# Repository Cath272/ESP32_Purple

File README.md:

# ESP32_Purple

The ESP32 PURPLE was build because i wanted to design my own esp32 based microcontroller with a few extra features.

Features:
-Esp32 Module,

-CH343P usb to uart Ic,

-3.3V AMS117 power supply,

-USB TYPE-C port with c to c cable support, 

-MicroSD card slot,

-14Pin Connector for a ST7735 Display(0.5mm pitch),

PCB view:

Schematic:

Components Pinout:

LCD: DC:IO26 , MOSI:IO23, SCK:IO18, CS:IO5

MicroSD: MISO:IO19, SCK:IO18, MOSI:IO23 , CS_SD:IO5

Final Assembled product:

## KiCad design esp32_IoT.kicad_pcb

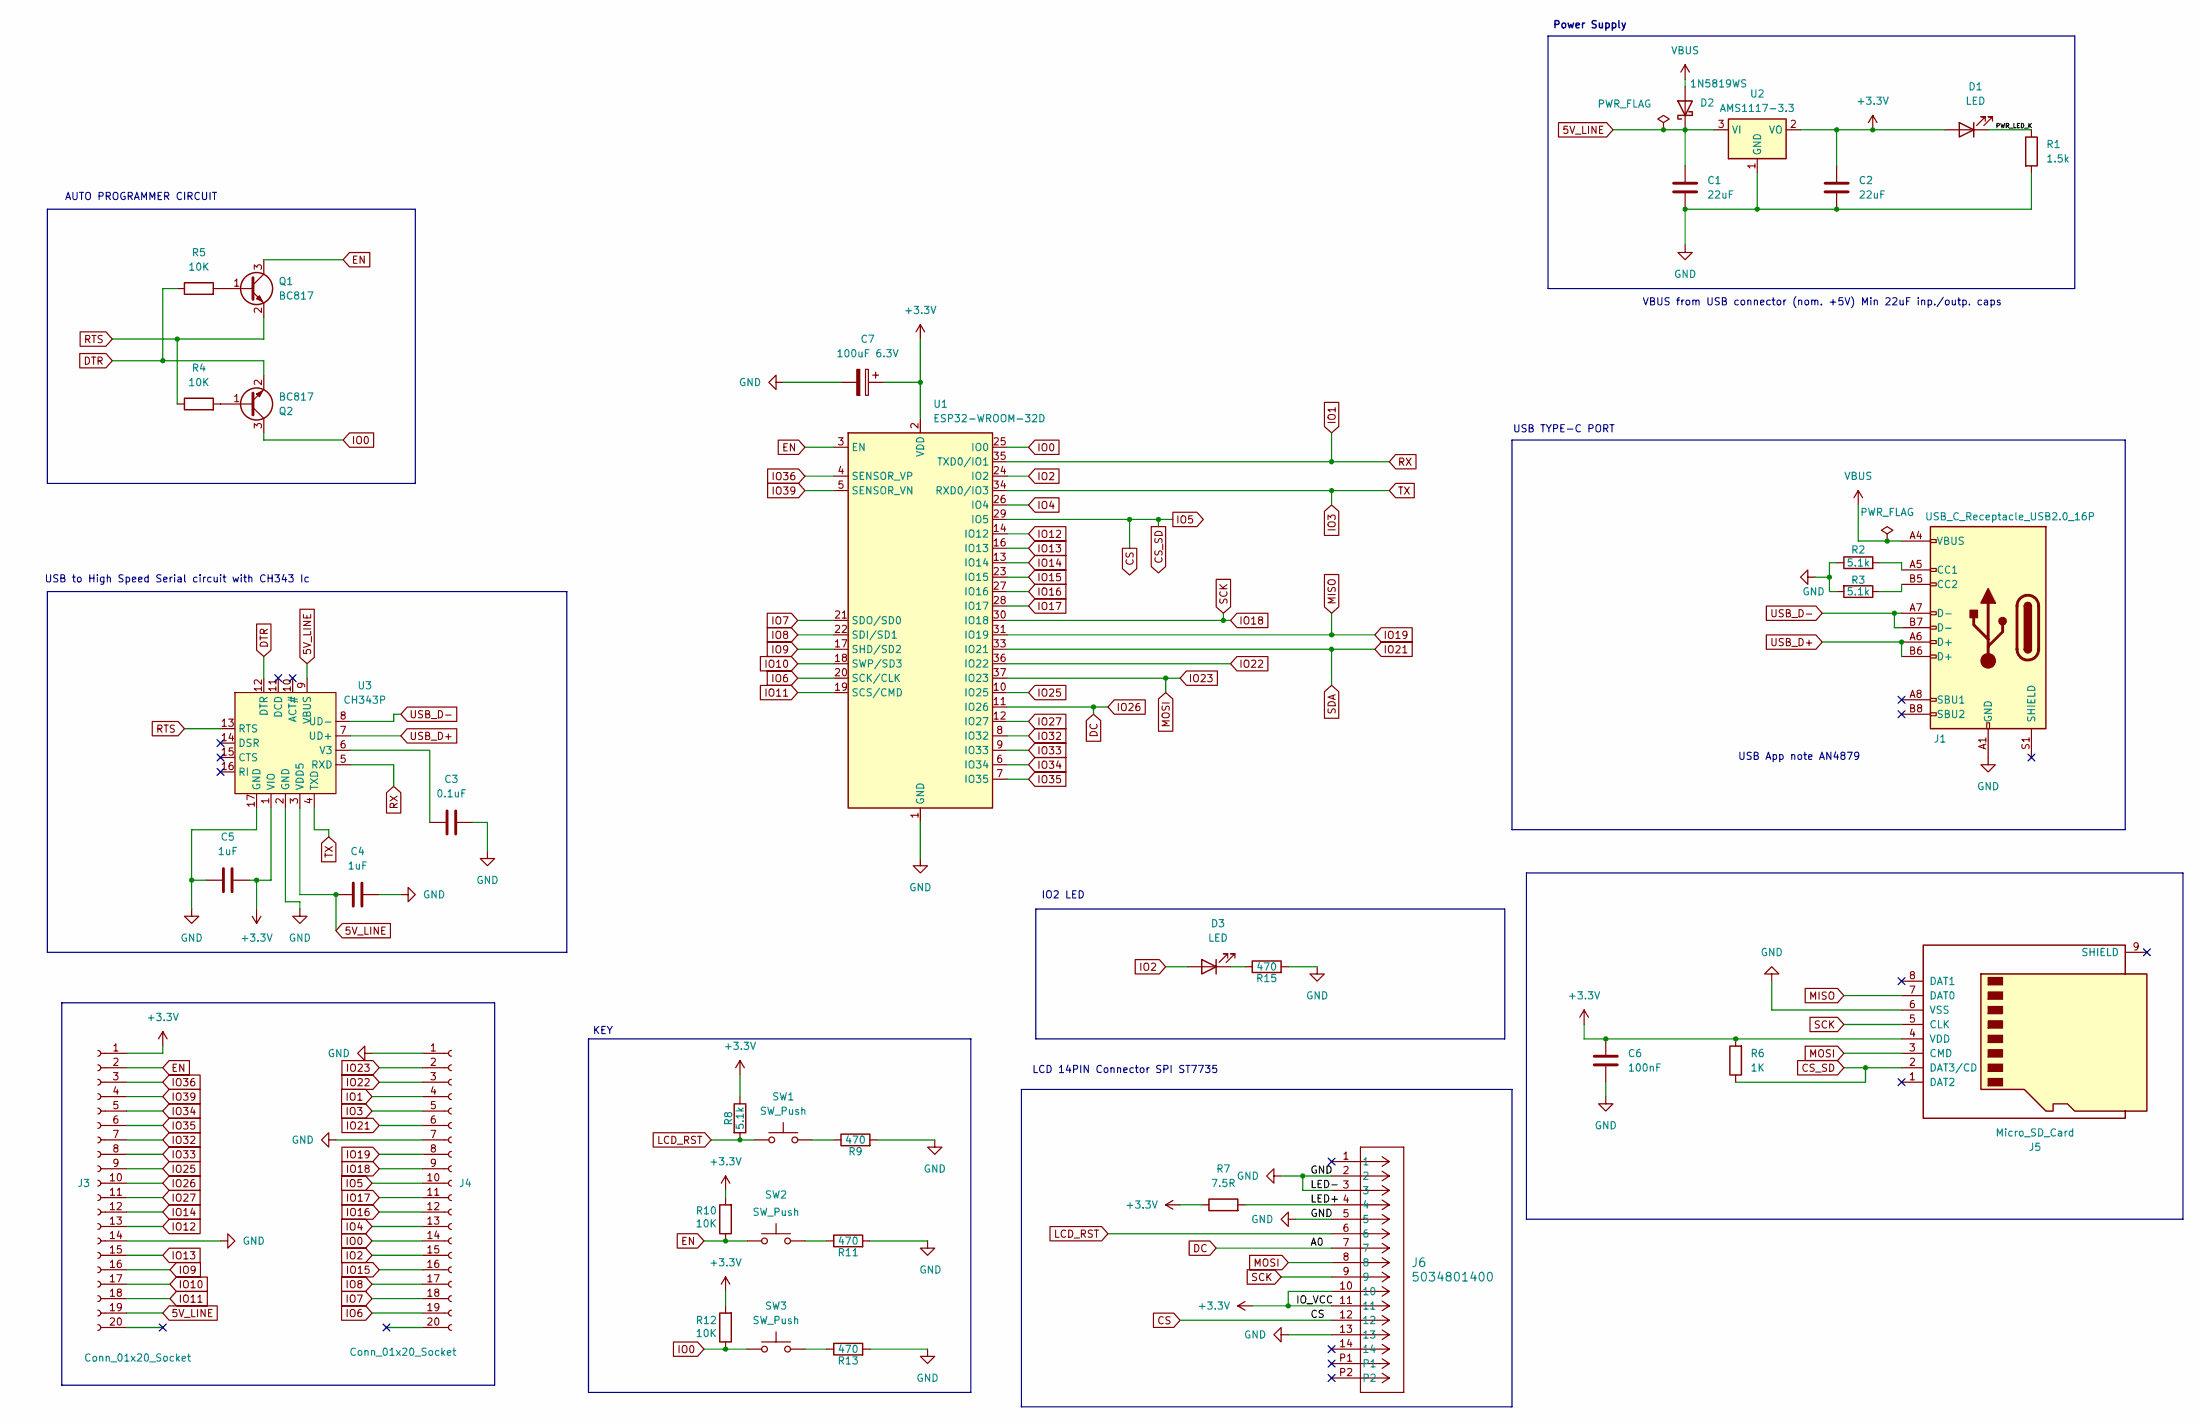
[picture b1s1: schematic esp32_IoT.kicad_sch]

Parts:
C1, C2: 22uF; C_0805_2012Metric
C3: 0.1uF; C_0402_1005Metric
C4, C5: 1uF; C_0402_1005Metric
C6: 100nF; C_0402_1005Metric_Pad0.74x0.62mm_HandSolder
C7: 100uF 6.3V; CP_EIA-3528-15_AVX-H_Pad1.50x2.35mm_HandSolder
D1, D3: LED; LED_0603_1608Metric
D2: 1N5819WS; D_SOD-323
J1: USB_C_Receptacle_USB2.0_16P; USB_C_Receptacle_GCT_USB4105-xx-A_16P_TopMnt_Horizontal
J3, J4: Conn_01x20_Socket; PinSocket_1x20_P2.54mm_Vertical
J5: Micro_SD_Card; SUNTECH_ST-TF-003A
J6: 5034801400; Hirose_FH12-14S-0.5SH_1x14-1MP_P0.50mm_Horizontal
Q1, Q2: BC817; SOT-23
R1: 1.5k; R_0402_1005Metric
R2, R3, R8: 5.1k; R_0402_1005Metric
R4, R5, R10, R12: 10K; R_0402_1005Metric
R6: 1K; R_0402_1005Metric
R7: 7.5R; R_0402_1005Metric
R9, R11, R13, R15: 470; R_0402_1005Metric
SW1, SW2, SW3: SW_Push; SW_SPST_PTS810
U1: ESP32-WROOM-32D
U2: AMS1117-3.3; SOT-223-3_TabPin2
U3: CH343P; TQFN-16-1EP_3x3mm_P0.5mm_EP1.6x1.6mm

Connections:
5V_LINE: C1.1, C4.1, D2.1 (K), J3.19, U2.3 (VI), U3.3 (VDD5), U3.9 (VBUS)
+3.3V: C2.1, C5.2, C6.1, C7.1, D1.2 (A), J3.1, J5.4 (VDD), J6.10, J6.11, R6.2, R7.1, R8.1, R10.2, R12.2, U1.2 (VDD), U2.2 (VO), U3.1 (VIO)
/LED+: J6.4, R7.2
/PWR_LED_K: D1.1 (K), R1.1
CS: J4.10, J5.2 (DAT3/CD), J6.12, R6.1, U1.29 (IO5)
DC: J3.10, J6.7, U1.11 (IO26)
DTR: Q2.2 (E), R5.1, U3.12 (DTR)
EN: J3.2, Q1.3 (C), R10.1, SW2.1, U1.3 (EN)
GND: C1.2, C2.2, C3.2, C4.2, C5.1, C6.2, C7.2, J1.A1 (GND), J1.A12 (GND), J1.B1 (GND), J1.B12 (GND), J3.14, J4.1, J4.7, J5.6 (VSS), J6.2, J6.3, J6.5, J6.13, R1.2, R2.1, R3.2, R9.2, R11.2, R13.2, R15.2, U1.1 (GND), U1.15 (GND), U1.38 (GND), U1.39 (GND), U2.1 (GND), U3.2 (GND), U3.17 (GND)
IO0: J4.14, Q2.3 (C), R12.1, SW3.1, U1.25 (IO0)
IO1: J4.4, U1.35 (TXD0/IO1), U3.5 (RXD)
IO2: D3.2 (A), J4.15, U1.24 (IO2)
IO3: J4.5, U1.34 (RXD0/IO3), U3.4 (TXD)
IO4: J4.13, U1.26 (IO4)
IO6: J4.19, U1.20 (SCK/CLK)
IO7: J4.18, U1.21 (SDO/SD0)
IO8: J4.17, U1.22 (SDI/SD1)
IO9: J3.16, U1.17 (SHD/SD2)
IO10: J3.17, U1.18 (SWP/SD3)
IO11: J3.18, U1.19 (SCS/CMD)
IO12: J3.13, U1.14 (IO12)
IO13: J3.15, U1.16 (IO13)
IO14: J3.12, U1.13 (IO14)
IO15: J4.16, U1.23 (IO15)
IO16: J4.12, U1.27 (IO16)
IO17: J4.11, U1.28 (IO17)
IO18: J4.9, J5.5 (CLK), J6.9, U1.30 (IO18)
IO19: J4.8, J5.7 (DAT0), U1.31 (IO19)
IO21: J4.6, U1.33 (IO21)
IO22: J4.3, U1.36 (IO22)
IO23: J4.2, J5.3 (CMD), J6.8, U1.37 (IO23)
IO25: J3.9, U1.10 (IO25)
IO27: J3.11, U1.12 (IO27)
IO32: J3.7, U1.8 (IO32)
IO33: J3.8, U1.9 (IO33)
IO34: J3.5, U1.6 (IO34)
IO35: J3.6, U1.7 (IO35)
IO36: J3.3, U1.4 (SENSOR_VP)
IO39: J3.4, U1.5 (SENSOR_VN)
LCD_RST: J6.6, R8.2, SW1.1; also elsewhere on the board
unnamed: D3.1 (K), R15.1
unnamed: J1.A5 (CC1), R2.2
unnamed: J1.B5 (CC2), R3.1
unnamed: Q1.1 (B), R5.2
unnamed: Q2.1 (B), R4.2
unnamed 45: R9.1, SW1.2; also elsewhere on the board
unnamed: R11.1, SW2.2
unnamed: R13.1, SW3.2
unnamed: C3.1, U3.6 (V3)
RTS: Q1.2 (E), R4.1, U3.13 (RTS)
USB_D+: J1.A6 (D+), J1.B6 (D+), U3.7 (UD+)
USB_D-: J1.A7 (D-), J1.B7 (D-), U3.8 (UD-)
VBUS: D2.2 (A), J1.A4 (VBUS), J1.A9 (VBUS), J1.B4 (VBUS), J1.B9 (VBUS)

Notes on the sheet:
LCD 14PIN Connector SPI ST7735
KEY
IO2 LED
USB to High Speed Serial circuit with CH343 Ic
AUTO PROGRAMMER CIRCUIT
VBUS from USB connector (nom. +5V) Min 22uF inp./outp. caps
USB App note AN4879
Power Supply
USB TYPE-C PORT

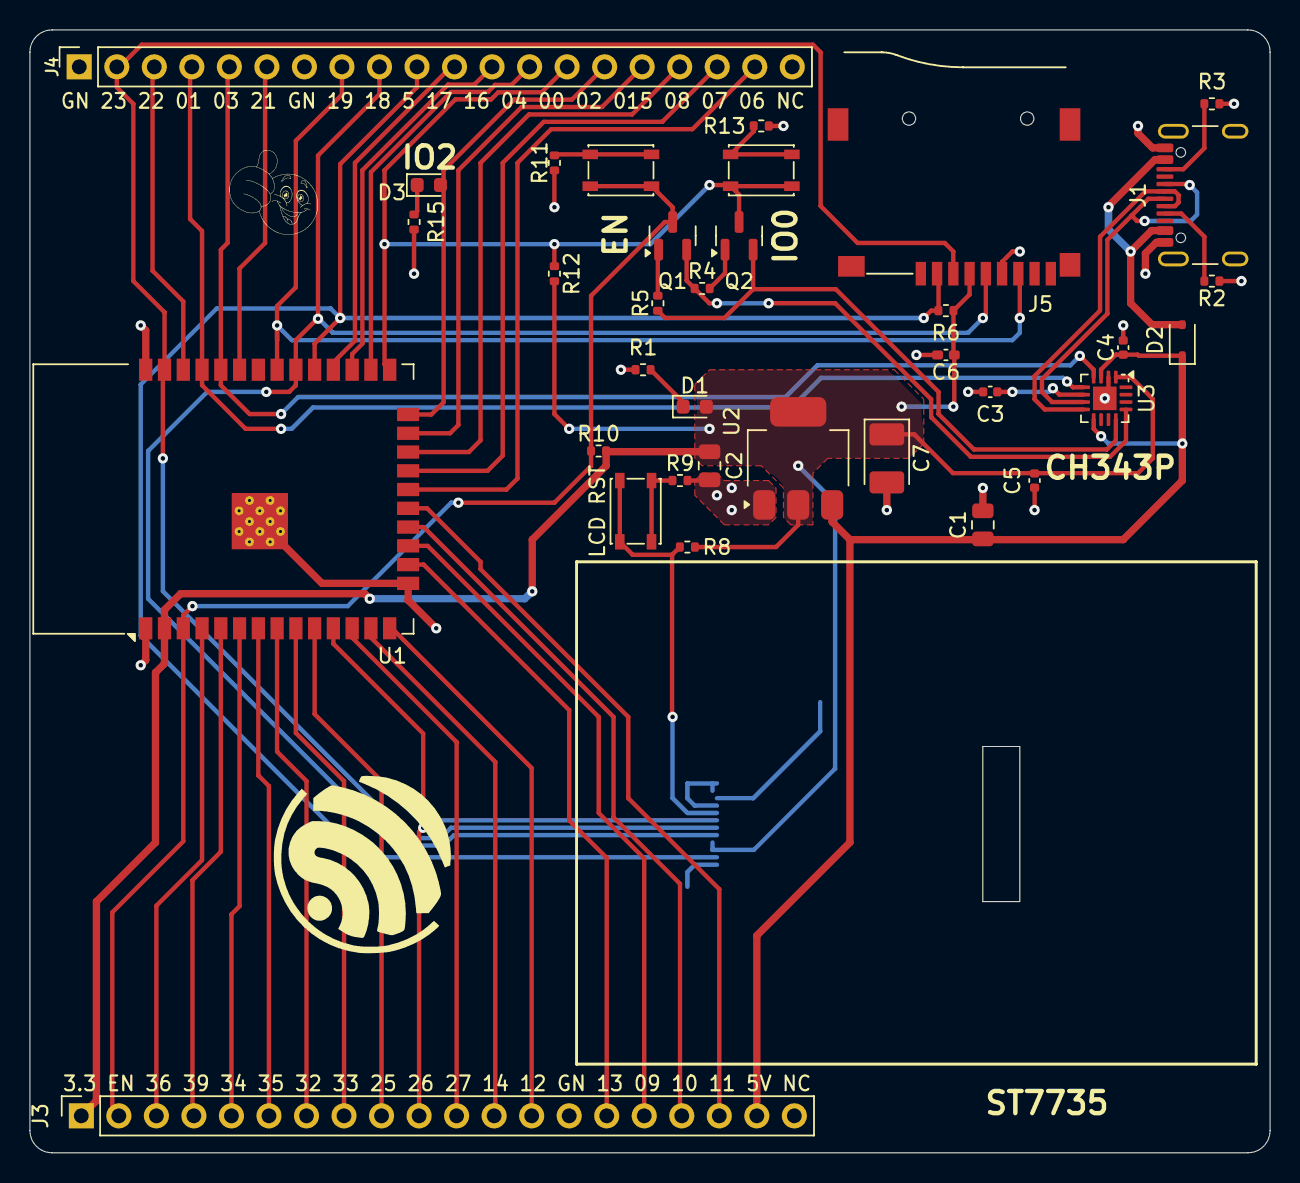
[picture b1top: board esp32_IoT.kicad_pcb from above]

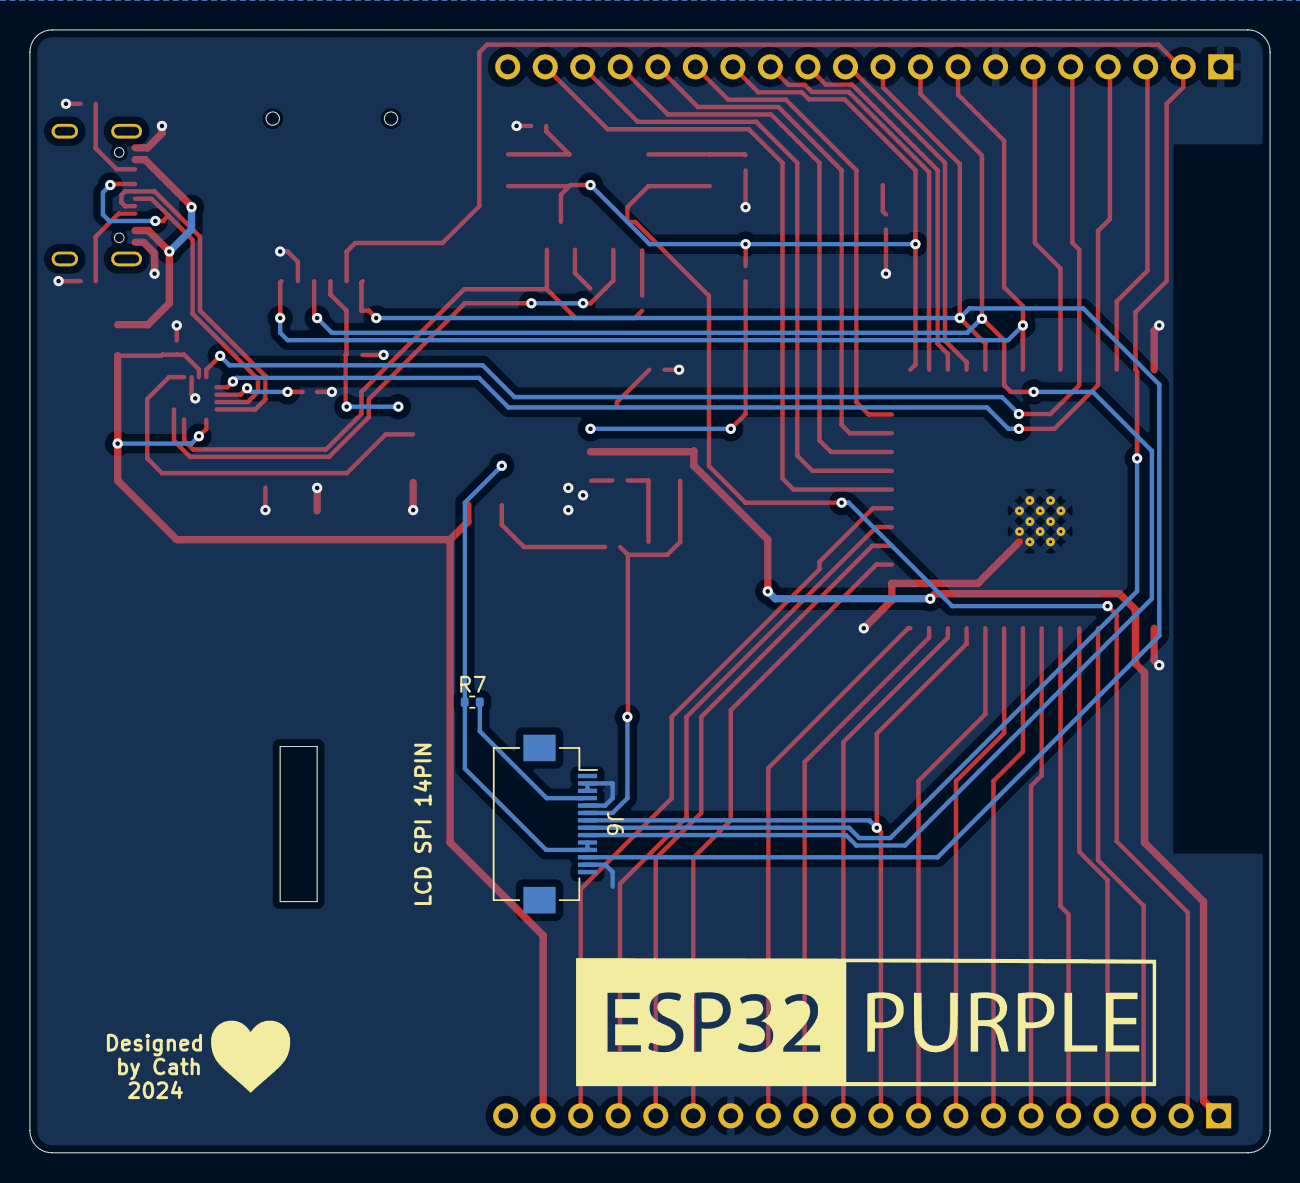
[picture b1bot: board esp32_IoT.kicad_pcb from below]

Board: 2 copper layers, 83.9 x 76.0 mm, 37 parts (2 on the bottom side), 53 nets.

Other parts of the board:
LCD RST: SW_Push; SW_SPST_PTS810

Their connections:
LCD_RST: LCD RST.1; also elsewhere on the board
unnamed 45: LCD RST.2; also elsewhere on the board

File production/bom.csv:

Designator,Footprint,Quantity,Value,LCSC Part #
"C1, C2",0805,2,22uF,
C3,0402,1,0.1uF,
"C4, C5",0402,2,1uF,
C6,0402,1,100nF,
C7,CP_EIA-3528-15_AVX-H_Pad1.50x2.35mm_HandSolder,1,100uF 6.3V,
"D1, D3",0603,2,LED,
D2,D_SOD-323,1,1N5819WS,
J1,USB_C_Receptacle_GCT_USB4105-xx-A_16P_TopMnt_Horizontal,1,USB_C_Receptacle_USB2.0_16P,
"J3, J4",PinSocket_1x20_P2.54mm_Vertical,2,Conn_01x20_Socket,
J5,SUNTECH_ST-TF-003A,1,Micro_SD_Card,
J6,Hirose_FH12-14S-0.5SH_1x14-1MP_P0.50mm_Horizontal,1,5034801400,
"LCD RST, SW2, SW3",SW_SPST_PTS810,3,SW_Push,
"Q1, Q2",SOT-23,2,BC817,
R1,0402,1,1.5k,
"R10, R12, R4, R5",0402,4,10K,
"R11, R13, R15, R9",0402,4,470,
"R2, R3, R8",0402,3,5.1k,
R6,0402,1,1K,
R7,0402,1,7.5R,
U1,ESP32-WROOM-32D,1,ESP32-WROOM-32D,
U2,SOT-223-3_TabPin2,1,AMS1117-3.3,
U3,TQFN-16-1EP_3x3mm_P0.5mm_EP1.6x1.6mm,1,CH343P,
